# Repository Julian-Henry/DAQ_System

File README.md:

# DAQ_System

# Project Showcase Link
https://eecs.engineering.oregonstate.edu/project-showcase/projects/?id=z2oxjPZD8s8oi1AW

# Project Overview
The purpose of the personal data acquisition prototype project is to design a data recorder prototype for a general consumer target market. This prototype was designed to be used with a go-kart. Sensors can be connected to the data recorder in a modular fashion. Sensor modules were developed on custom-designed PCBs that utilize STM32 microcontrollers. Each microcontroller sends data to a database hosted on a Raspberry Pi. The data can then be outputted to the user through an intuitive UI. The firmware for the microcontrollers was developed using the RUST programming language. The database used SQLite. The UI was made using the EGUI framework in RUST. Some notable achievements include the UI and firmware development using Rust, a cutting-edge secure programming language, and the modularity of the system which allows for a variety of sensor configurations based on the user's preferences. Key challenges revolved around the creation of custom STM32-based PCBs, suggesting one key area for future improvement.

## System setup guide

Materials: 
  - Raspberry Pi with monitor, keyboard, and mouse. Make sure Its micro SD card has more than 8GB of space

  - RS485 CAN Hat

  - “Sensor modules” 

.

Steps:

1. Use the RS485 CAN Hat on the Pi. Connect sensor modules.

2. Flash code to the Nucleo dev boards that are in charge of the sensors (files in the nucleo_firmware directory).

3. Set up the CAN Hat on the Pi:

  // Open the Raspberry Pi terminal and run the following commands:
  wget https://github.com/joan2937/lg/archive/master.zip 
  unzip master.zip
  cd lg-master
  sudo make install
  
  sudo apt-get update
  sudo apt-get install python-serial
  sudo pip install python-can 
    //if it gives an error, run: rm /usr/lib/python3.11/EXTERNALLY-MANAGED
  sudo nano /boot/config.txt
  //in the file, Modify/create:
  dtparam=spi=on
  dtoverlay=mcp2515-can0,oscillator=12000000,interrupt=25,spimaxfrequency=2000000

  sudo reboot  //NOTE: you have to have the CAN hat connected before the Pi reboots
  
  //Finally, test that it knows the CAN is there:
  	dmesg | grep -i '\(can\|spi\)'

4. Copy the daq_gui_1 & logger_code directories to the Pi

5. Run the pi_can.py file in the logger_code directory to start the communication. You should see the data being sent in the terminal if it is working.

6. Go to the daq_gui_1 directory and run the daq_gui code (Use cargo run --release if it doesn’t work the normal way). It will take a long time to run the first time.

7. Done. It should work!

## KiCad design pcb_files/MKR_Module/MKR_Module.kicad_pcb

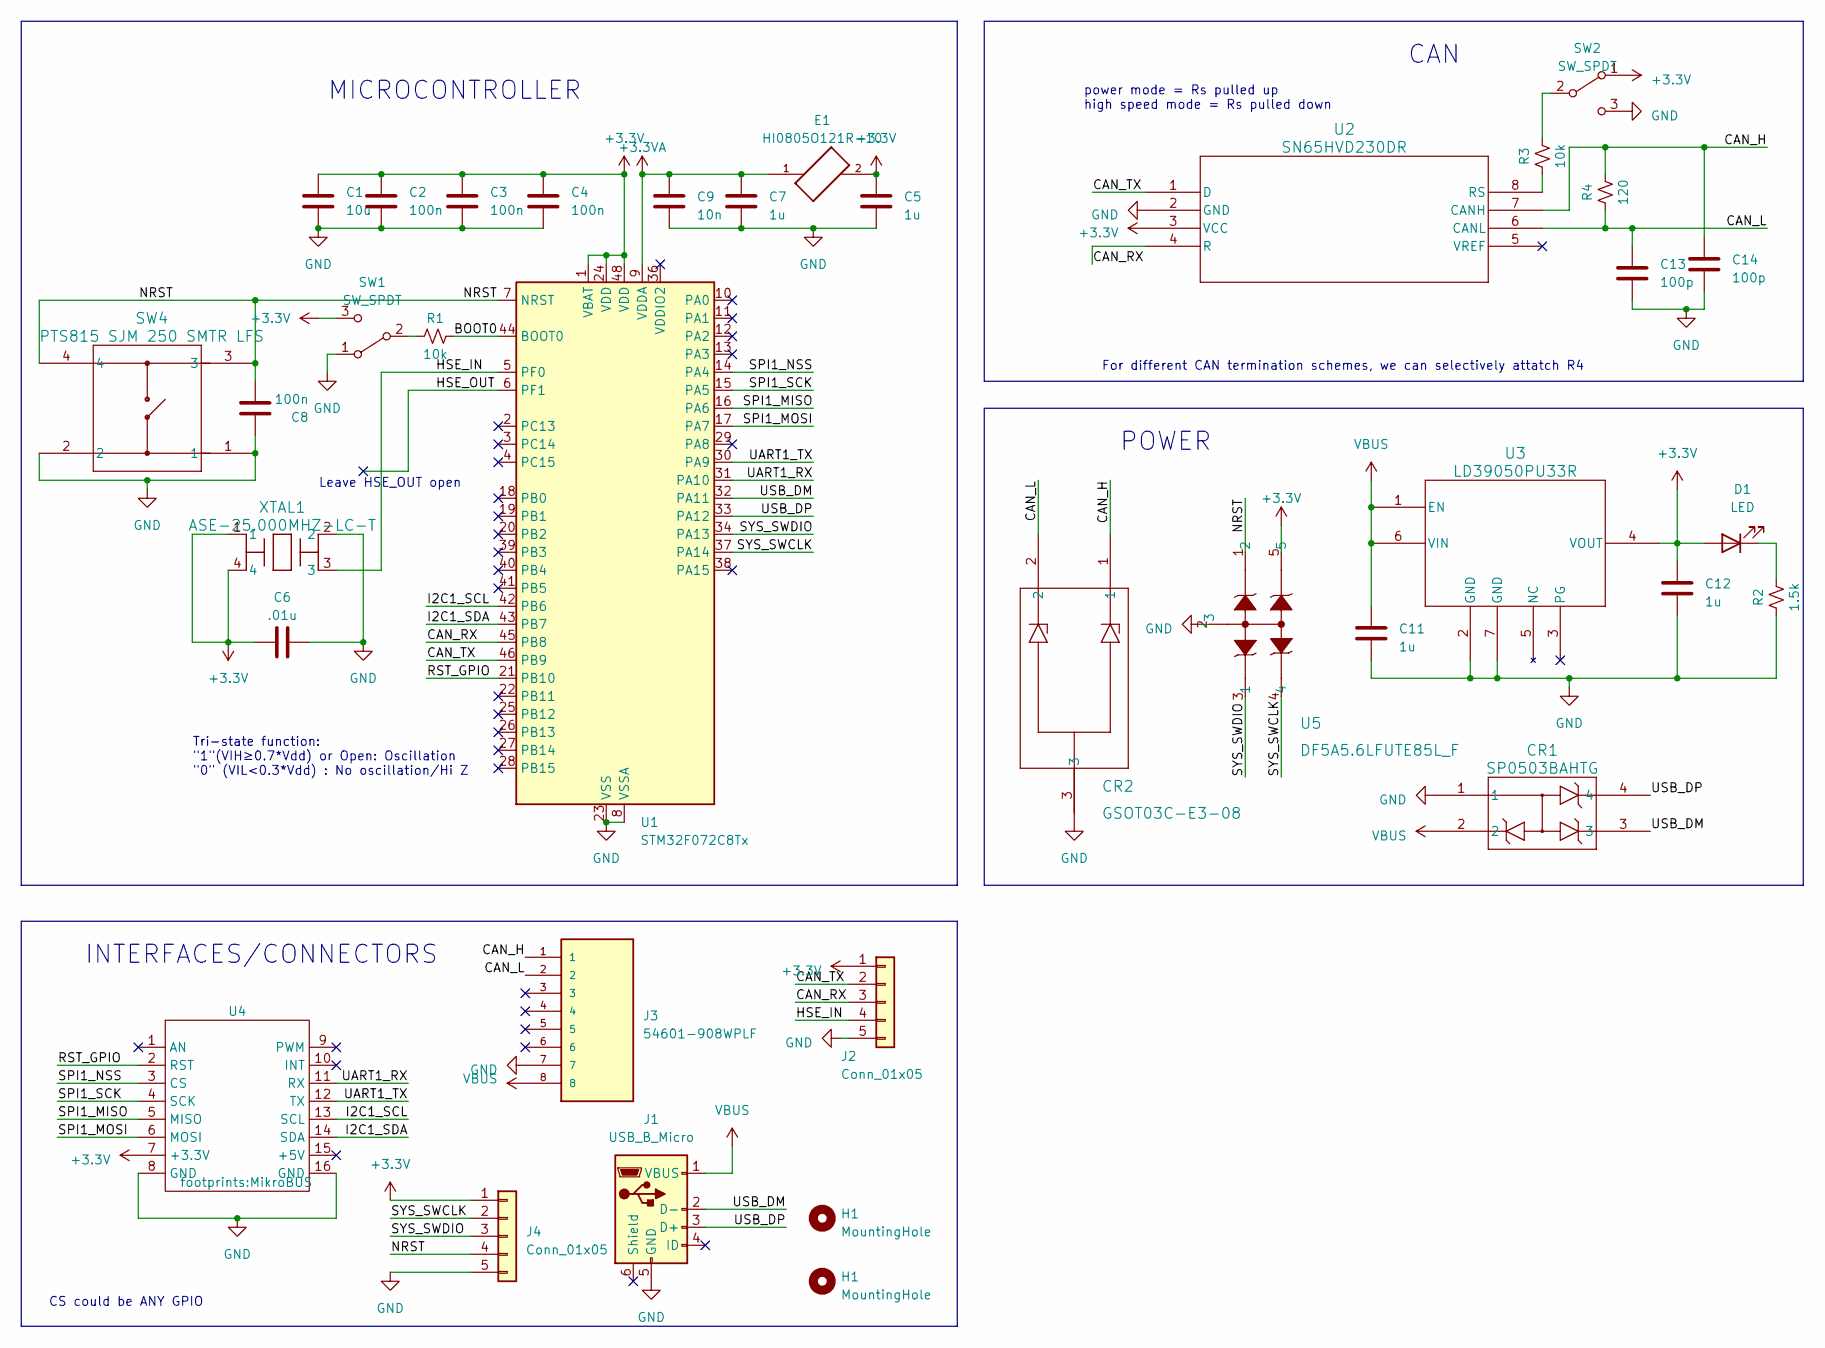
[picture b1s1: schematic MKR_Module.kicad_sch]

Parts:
C1: 10u; R_0805_2012Metric_Pad1.20x1.40mm_HandSolder
C2, C3, C4, C8: 100n; R_0805_2012Metric_Pad1.20x1.40mm_HandSolder
C5, C7, C11, C12: 1u; R_0805_2012Metric_Pad1.20x1.40mm_HandSolder
C6: .01u; R_0805_2012Metric_Pad1.20x1.40mm_HandSolder
C9: 10n; R_0805_2012Metric_Pad1.20x1.40mm_HandSolder
C13, C14: 100p; R_0805_2012Metric_Pad1.20x1.40mm_HandSolder
CR1: SP0503BAHTG; TVS-SP05_LTF-L
CR2: GSOT03C-E3-08; SOT_03C-E3-08_VIS
D1: LED; R_0805_2012Metric_Pad1.20x1.40mm_HandSolder
E1: HI0805O121R-10; FB_HI0805O121R-10
H1: MountingHole; MountingHole_2.5mm; Digikey Link N/A
J1: USB_B_Micro; AMPHENOL_10118194-0001LF
J2, J4: Conn_01x05; PinHeader_1x05_P2.54mm_Vertical
J3: 54601-908WPLF; AMPHENOL_54601-908WPLF; PARTREV F
R1, R3: 10k; R_0805_2012Metric_Pad1.20x1.40mm_HandSolder
R2: 1.5k; R_0805_2012Metric_Pad1.20x1.40mm_HandSolder
R4: 120; R_0805_2012Metric_Pad1.20x1.40mm_HandSolder
SW1, SW2: SW_SPDT; 1825232-1_TEC
SW4: PTS815 SJM 250 SMTR LFS; SW4_PTS815 SJM 250 SMTR LFS_CNK
U1: STM32F072C8Tx; LQFP-48_7x7mm_P0.5mm
U2: SN65HVD230DR; D8-L
U3: LD39050PU33R; DFN6_3X3_STM-L
U4: MikroBUS
U5: DF5A5.6LFUTE85L_F; SOT-353 USV_TOS
XTAL1: ASE-25.000MHZ-LC-T; CHIP_ASE-24_ABR-L

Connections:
+3.3V: C1.1, C2.1, C3.1, C4.1, C5.1, C6.2, C12.1, D1.2 (A), E1.2, J2.1, J4.1, SW1.3 (C), SW2.1 (A), U1.1 (VBAT), U1.24 (VDD), U1.48 (VDD), U2.3 (VCC), U3.4 (VOUT), U4.7 (+3.3V), U5.5, XTAL1.1, XTAL1.4
+3.3VA: C7.1, C9.1, E1.1, U1.9 (VDDA)
/BOOT0: R1.2, U1.44 (BOOT0)
/CAN_H: C14.1, CR2.1, J3.1, R4.2, U2.7 (CANH)
/CAN_L: C13.1, CR2.2, J3.2, R4.1, U2.6 (CANL)
/CAN_RX: J2.3, U1.45 (PB8), U2.4 (R)
/CAN_TX: J2.2, U1.46 (PB9), U2.1 (D)
/HSE_IN: J2.4, U1.5 (PF0), XTAL1.3
/HSE_OUT: U1.6 (PF1)
/I2C1_SCL: U1.42 (PB6), U4.13 (SCL)
/I2C1_SDA: U1.43 (PB7), U4.14 (SDA)
/NRST: C8.2, J4.4, SW4.3, SW4.4, U1.7 (NRST), U5.1 (2)
/RST_GPIO: U1.21 (PB10), U4.2 (RST)
/SPI1_MISO: U1.16 (PA6), U4.5 (MISO)
/SPI1_MOSI: U1.17 (PA7), U4.6 (MOSI)
/SPI1_NSS: U1.14 (PA4), U4.3 (CS)
/SPI1_SCK: U1.15 (PA5), U4.4 (SCK)
/SYS_SWCLK: J4.2, U1.37 (PA14), U5.4
/SYS_SWDIO: J4.3, U1.34 (PA13), U5.3 (1)
/UART1_RX: U1.31 (PA10), U4.11 (RX)
/UART1_TX: U1.30 (PA9), U4.12 (TX)
/USB_DM: CR1.3, J1.2 (D-), U1.32 (PA11)
/USB_DP: CR1.4, J1.3 (D+), U1.33 (PA12)
GND: C1.2, C2.2, C3.2, C4.2, C5.2, C6.1, C7.2, C8.1, C9.2, C11.2, C12.2, C13.2, C14.2, CR1.1, CR2.3, J1.5 (GND), J2.5, J3.7, J4.5, R2.1, SW1.1 (A), SW2.3 (C), SW4.1, SW4.2, U1.8 (VSSA), U1.23 (VSS), U1.35 (VSS), U1.47 (VSS), U2.2 (GND), U3.2 (GND), U3.7 (GND), U4.8 (GND), U4.16 (GND), U5.2 (3), XTAL1.2
unnamed: D1.1 (K), R2.2
unnamed: R1.1, SW1.2 (B)
unnamed: R3.2, SW2.2 (B)
unnamed: R3.1, U2.8 (RS)
VBUS: C11.1, CR1.2, J1.1 (VBUS), J3.8, U3.1 (EN), U3.6 (VIN)

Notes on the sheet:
POWER
CAN
power mode = Rs pulled up high speed mode = Rs pulled down
For different CAN termination schemes, we can selectively attatch R4
MICROCONTROLLER
Leave HSE_OUT open
INTERFACES/CONNECTORS
Tri-state function: "1"(VIH≥0.7*Vdd) or Open: Oscillation "0" (VIL<0.3*Vdd) : No oscillation/Hi Z
CS could be ANY GPIO

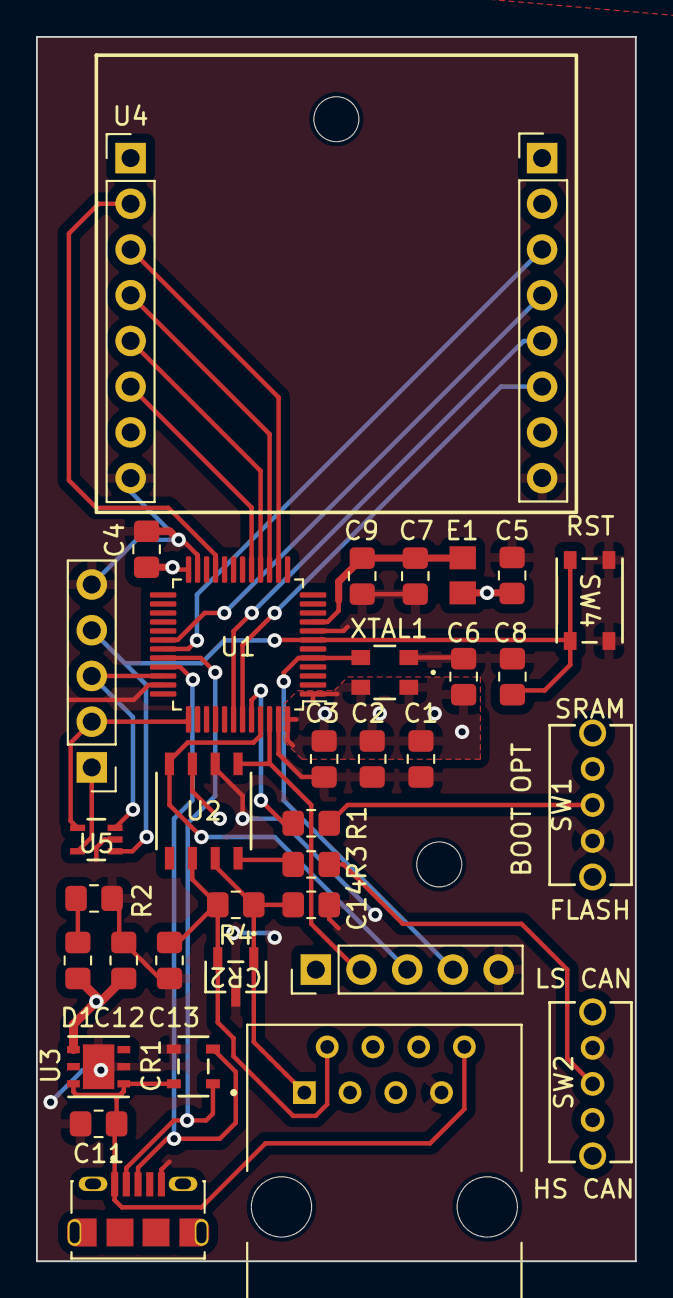
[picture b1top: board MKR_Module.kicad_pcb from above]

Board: 2 copper layers, 33.3 x 68.0 mm, 36 parts (0 on the bottom side), 28 nets.

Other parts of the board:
H2: MountingHole; MountingHole_2.5mm

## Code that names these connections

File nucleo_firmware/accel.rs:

#![no_std]
#![no_main]

//import libraries
use cortex_m::register::apsr::read;
use defmt::*;
use embassy_executor::Spawner;
use embassy_stm32::can::{
    bxcan::{filter::Mask32, Fifo, Frame, Interrupt, StandardId},
    Can, Rx0InterruptHandler, Rx1InterruptHandler, SceInterruptHandler, TxInterruptHandler,
};
use embassy_stm32::dma::NoDma;
use embassy_stm32::gpio::{Level, Output, Speed};
use embassy_stm32::i2c::I2c;
use embassy_stm32::interrupt;
use embassy_stm32::peripherals::CAN1;
use embassy_stm32::spi::{Config, Spi};
use embassy_stm32::time::Hertz;
use embassy_stm32::{bind_interrupts, i2c, peripherals};

use embassy_time::{Duration, Timer};
use embedded_hal::spi;
use {defmt_rtt as _, panic_probe as _};

//define address of the accelerometer
const ACCEL_ADDR: u8 = 0x1E;

//bind CAN interrupts
bind_interrupts!(struct Irqs {
    CAN1_RX0 => Rx0InterruptHandler<CAN1>;
    CAN1_RX1 => Rx1InterruptHandler<CAN1>;
    CAN1_SCE => SceInterruptHandler<CAN1>;
    CAN1_TX => TxInterruptHandler<CAN1>;
});

#[embassy_executor::main]
async fn main(_spawner: Spawner) {
    let p = embassy_stm32::init(Default::default());

    //create objects for the led and CAN bus
    let mut led = Output::new(p.PB7, Level::High, Speed::Low);
    let mut can = Can::new(p.CAN1, p.PD0, p.PD1, Irqs);

    //bind interrupts for I2C communication
    bind_interrupts!(struct Irqs2 {
        I2C1_EV => i2c::EventInterruptHandler<peripherals::I2C1>;
        I2C1_ER => i2c::ErrorInterruptHandler<peripherals::I2C1>;
    });

    // setup can
    can.as_mut()
        .modify_filters()
        .enable_bank(0, Fifo::Fifo0, Mask32::accept_all());

    can.as_mut().modify_config().leave_disabled();

    can.set_bitrate(100_000);

    can.enable().await;

    //configure i2c
    let mut i2c = I2c::new(
        p.I2C1,
        p.PB8,
        p.PB9,
        Irqs2,
        NoDma,
        NoDma,
        embassy_stm32::time::Hertz(100000),
        Default::default(),
    );
    // set digital out pins for microcontroller
    let mut reset_pin = Output::new(p.PA4, Level::Low, Speed::Low);

    //initialize data buffers
    let mut data_buffer: [u8; 13] = [0; 13];
    let mut accel_vals: [u8; 2] = [0; 2];

    // define communication commands
    let read_xyz_data: [u8; 1] = [0x33];

    //wait 1 sec
    Timer::after(Duration::from_millis(1000)).await;

    reset_pin.set_high();
    reset_pin.set_low();

    //wait 1 sec
    Timer::after(Duration::from_millis(1000)).await;

    //check that I2C protocol is working correctly
    match i2c.blocking_write_read(ACCEL_ADDR, &[0x0D], &mut data_buffer) {
        Ok(()) => info!("Whoami: {}", data_buffer[0]),
        // Err(Error::Timeout) => error!("Operation timed out"),
        Err(e) => error!("I2c Error: {:?}", e),
    }
    info!("Accel: {:?}", data_buffer);

    //place control register in standby mode
    i2c.blocking_write_read(ACCEL_ADDR, &[0x2A, 0x00], &mut data_buffer);
    //set magnometer to 8x oversampling
    i2c.blocking_write_read(ACCEL_ADDR, &[0x5B, 0x1F], &mut data_buffer);
    //enable magnetic reset after each cycle
    i2c.blocking_write_read(ACCEL_ADDR, &[0x5C, 0x20], &mut data_buffer);
    //set accelerometer to a range of +/-4g
    i2c.blocking_write_read(ACCEL_ADDR, &[0x0E, 0x01], &mut data_buffer);
    //enable sampling
    i2c.blocking_write_read(ACCEL_ADDR, &[0x2A, 0x0D], &mut data_buffer);

    loop {
        //blink led
        led.toggle();

        //read accelerometer and magnetic field values
        i2c.blocking_write_read(ACCEL_ADDR, &[0x00], &mut data_buffer);

        //copy acceleration values to accel_vals buffer
        accel_vals[0] = data_buffer[1];
        accel_vals[1] = data_buffer[2];
        /*         accel_vals[2] = data_buffer[3];
        accel_vals[3] = data_buffer[4];
        accel_vals[4] = data_buffer[5];
        accel_vals[5] = data_buffer[6];*/
        info!("Accel: {:?}", accel_vals);

        // transmit accelerometer data over can
        let tx_frame = Frame::new_data(unwrap!(StandardId::new(300)), accel_vals);
        can.write(&tx_frame).await;
        Timer::after(Duration::from_millis(1000)).await;
    }
}

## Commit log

2024-05-25 added PCB files
